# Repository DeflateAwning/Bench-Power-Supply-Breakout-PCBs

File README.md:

# Bench-Power-Supply-Breakout-PCBs
A couple of quick PCBs to use cheap bench power supplies easier/safer

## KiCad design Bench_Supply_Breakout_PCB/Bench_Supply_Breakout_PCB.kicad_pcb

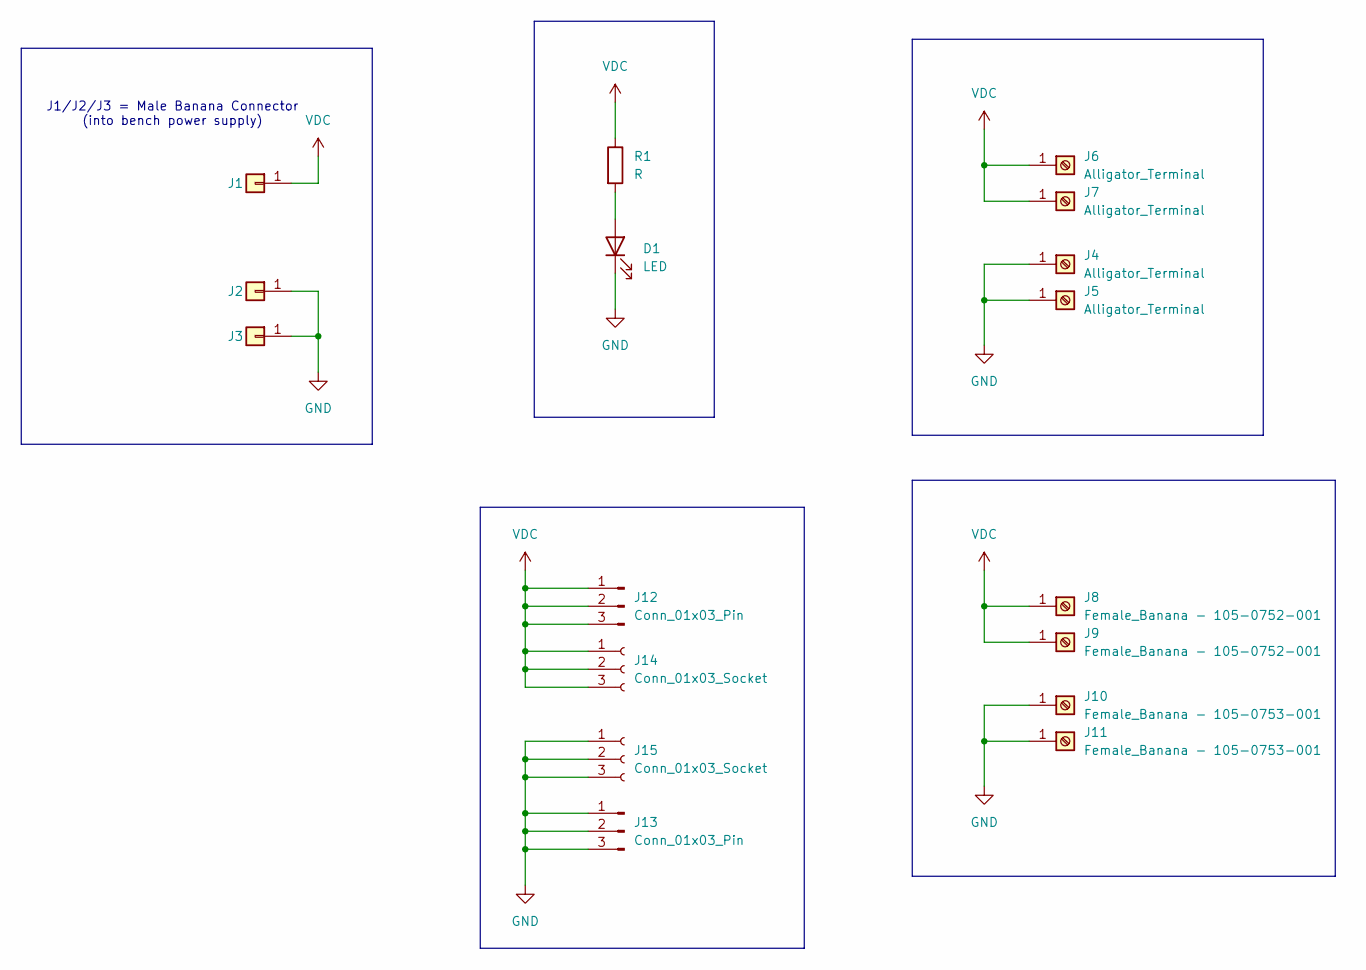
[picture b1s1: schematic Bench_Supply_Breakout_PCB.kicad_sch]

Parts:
D1: LED; LED_1206_3216Metric_Pad1.42x1.75mm_HandSolder
J1, J2, J3: Conn_01x01; MountingHole_3.2mm_M3_Pad
J4, J5, J6, J7: Alligator_Terminal; EdgeAlligatorConnector
J8, J9: Female_Banana - 105-0752-001; TestPoint_Bridge_Pitch5.08mm_Drill1.3mm
J10, J11: Female_Banana - 105-0753-001; TestPoint_Bridge_Pitch5.08mm_Drill1.3mm
J12, J13: Conn_01x03_Pin; PinHeader_1x03_P2.54mm_Vertical
J14, J15: Conn_01x03_Socket; PinSocket_1x03_P2.54mm_Vertical
R1: R; R_1206_3216Metric_Pad1.30x1.75mm_HandSolder

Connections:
GND: D1.1 (K), J2.1, J3.1, J4.1, J5.1, J10.1, J11.1, J13.1, J13.2, J13.3, J15.1, J15.2, J15.3
unnamed: D1.2 (A), R1.2
VDC: J1.1, J6.1, J7.1, J8.1, J9.1, J12.1, J12.2, J12.3, J14.1, J14.2, J14.3, R1.1

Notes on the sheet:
J1/J2/J3 = Male Banana Connector (into bench power supply)

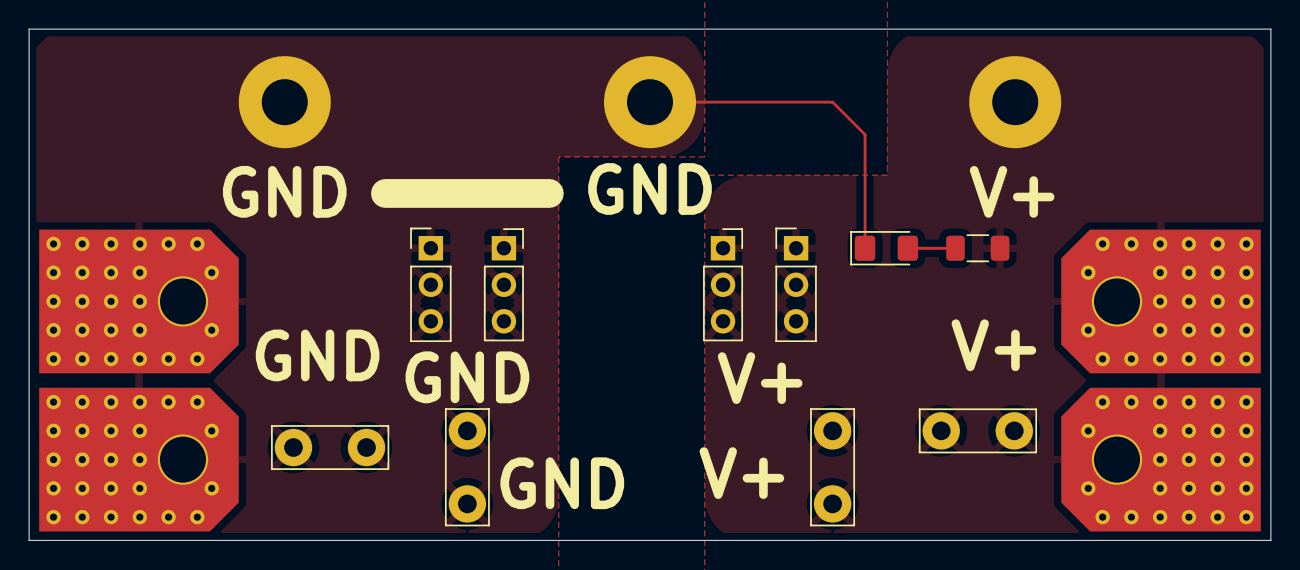
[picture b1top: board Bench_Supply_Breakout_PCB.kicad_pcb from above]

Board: 2 copper layers, 86.4 x 35.6 mm, 17 parts (0 on the bottom side), 3 nets.

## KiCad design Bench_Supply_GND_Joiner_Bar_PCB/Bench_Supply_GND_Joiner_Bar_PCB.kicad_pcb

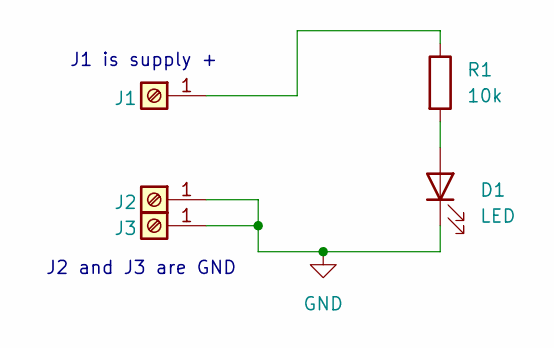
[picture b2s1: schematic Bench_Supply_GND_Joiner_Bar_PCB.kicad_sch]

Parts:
D1: LED; LED_1206_3216Metric_Pad1.42x1.75mm_HandSolder
J1, J2, J3: Screw_Terminal_01x01; Bench_Supply_Slot_D6.4mm_L10mm
R1: 10k; R_1206_3216Metric_Pad1.30x1.75mm_HandSolder

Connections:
GND: D1.1 (K), J2.1, J3.1
unnamed: D1.2 (A), R1.2
unnamed: J1.1, R1.1

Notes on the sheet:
J1 is supply +
J2 and J3 are GND

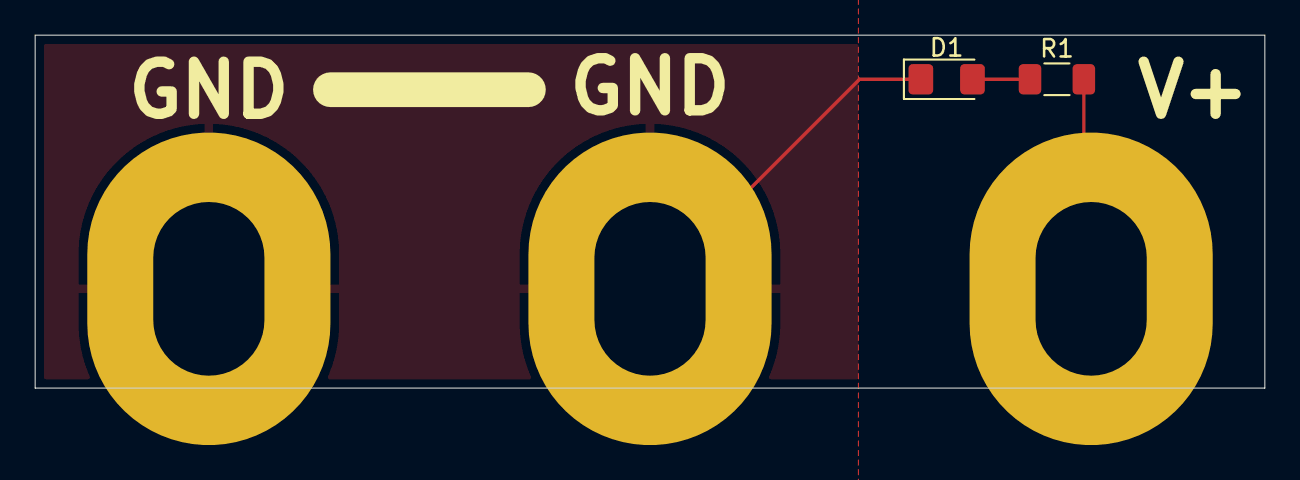
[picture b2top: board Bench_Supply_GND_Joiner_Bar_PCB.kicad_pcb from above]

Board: 2 copper layers, 70.8 x 20.3 mm, 5 parts (0 on the bottom side), 3 nets.

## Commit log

2025-06-14 Add licence: CERN Open Hardware Licence Version 2 - Permissive
2025-06-14 Create Bench_Supply_GND_Joiner_Bar_PCB
2025-06-15 Create breakout PCB
